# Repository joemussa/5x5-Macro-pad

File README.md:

# 5x5 Macro pad
 5x5 Macro Pad

1 Pi Pico
25 1N4148 SOD-323 (I'm an idiot and used 0805 footprint for the diodes but SOD-323 should fit this footprint)
25 Kailh MX Hotswap

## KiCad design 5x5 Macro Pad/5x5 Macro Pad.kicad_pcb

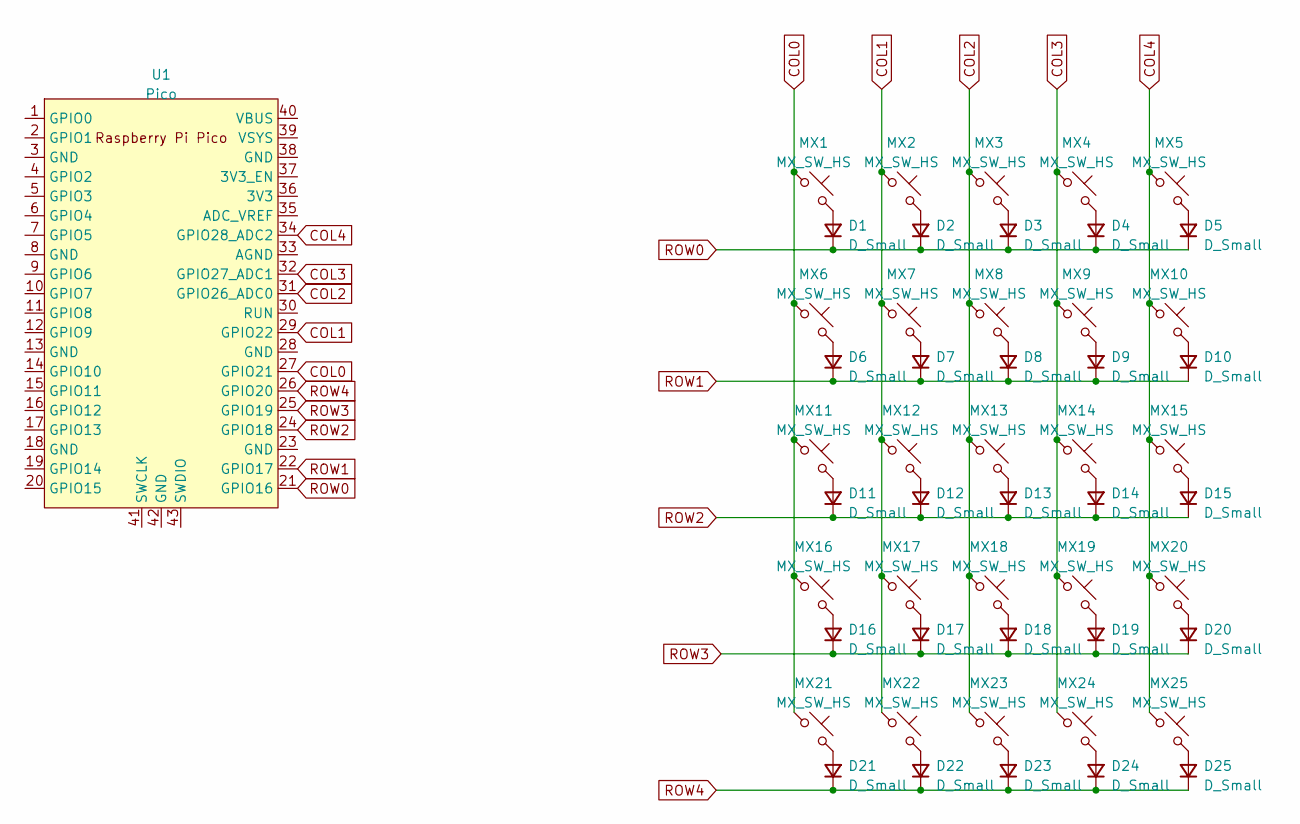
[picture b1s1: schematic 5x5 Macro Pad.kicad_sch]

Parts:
D1, D2, D3, D4, D5, D6, D7, D8, D9, D10, D11, D12, D13, D14, D15, D16, D17, D18, D19, D20, D21, D22, D23, D24, D25: D_Small; D_0805_2012Metric_Pad1.15x1.40mm_HandSolder
MX1, MX2, MX3, MX4, MX5, MX6, MX7, MX8, MX9, MX10, MX11, MX12, MX13, MX14, MX15, MX16, MX17, MX18, MX19, MX20, MX21, MX22, MX23, MX24, MX25: MX_SW_HS; SW_MX_HS_1u
U1: Pico; RPi_Pico_SMD_TH

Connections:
COL0: MX1.1, MX6.1, MX11.1, MX16.1, MX21.1, U1.27 (GPIO21)
COL1: MX2.1, MX7.1, MX12.1, MX17.1, MX22.1, U1.29 (GPIO22)
COL2: MX3.1, MX8.1, MX13.1, MX18.1, MX23.1, U1.31 (GPIO26_ADC0)
COL3: MX4.1, MX9.1, MX14.1, MX19.1, MX24.1, U1.32 (GPIO27_ADC1)
COL4: MX5.1, MX10.1, MX15.1, MX20.1, MX25.1, U1.34 (GPIO28_ADC2)
unnamed: D1.2 (A), MX1.2
unnamed: D2.2 (A), MX2.2
unnamed: D3.2 (A), MX3.2
unnamed: D4.2 (A), MX4.2
unnamed: D5.2 (A), MX5.2
unnamed: D6.2 (A), MX6.2
unnamed: D7.2 (A), MX7.2
unnamed: D8.2 (A), MX8.2
unnamed: D9.2 (A), MX9.2
unnamed: D10.2 (A), MX10.2
unnamed: D11.2 (A), MX11.2
unnamed: D12.2 (A), MX12.2
unnamed: D13.2 (A), MX13.2
unnamed: D14.2 (A), MX14.2
unnamed: D15.2 (A), MX15.2
unnamed: D16.2 (A), MX16.2
unnamed: D17.2 (A), MX17.2
unnamed: D18.2 (A), MX18.2
unnamed: D19.2 (A), MX19.2
unnamed: D20.2 (A), MX20.2
unnamed: D21.2 (A), MX21.2
unnamed: D22.2 (A), MX22.2
unnamed: D23.2 (A), MX23.2
unnamed: D24.2 (A), MX24.2
unnamed: D25.2 (A), MX25.2
ROW0: D1.1 (K), D2.1 (K), D3.1 (K), D4.1 (K), D5.1 (K), U1.21 (GPIO16)
ROW1: D6.1 (K), D7.1 (K), D8.1 (K), D9.1 (K), D10.1 (K), U1.22 (GPIO17)
ROW2: D11.1 (K), D12.1 (K), D13.1 (K), D14.1 (K), D15.1 (K), U1.24 (GPIO18)
ROW3: D16.1 (K), D17.1 (K), D18.1 (K), D19.1 (K), D20.1 (K), U1.25 (GPIO19)
ROW4: D21.1 (K), D22.1 (K), D23.1 (K), D24.1 (K), D25.1 (K), U1.26 (GPIO20)

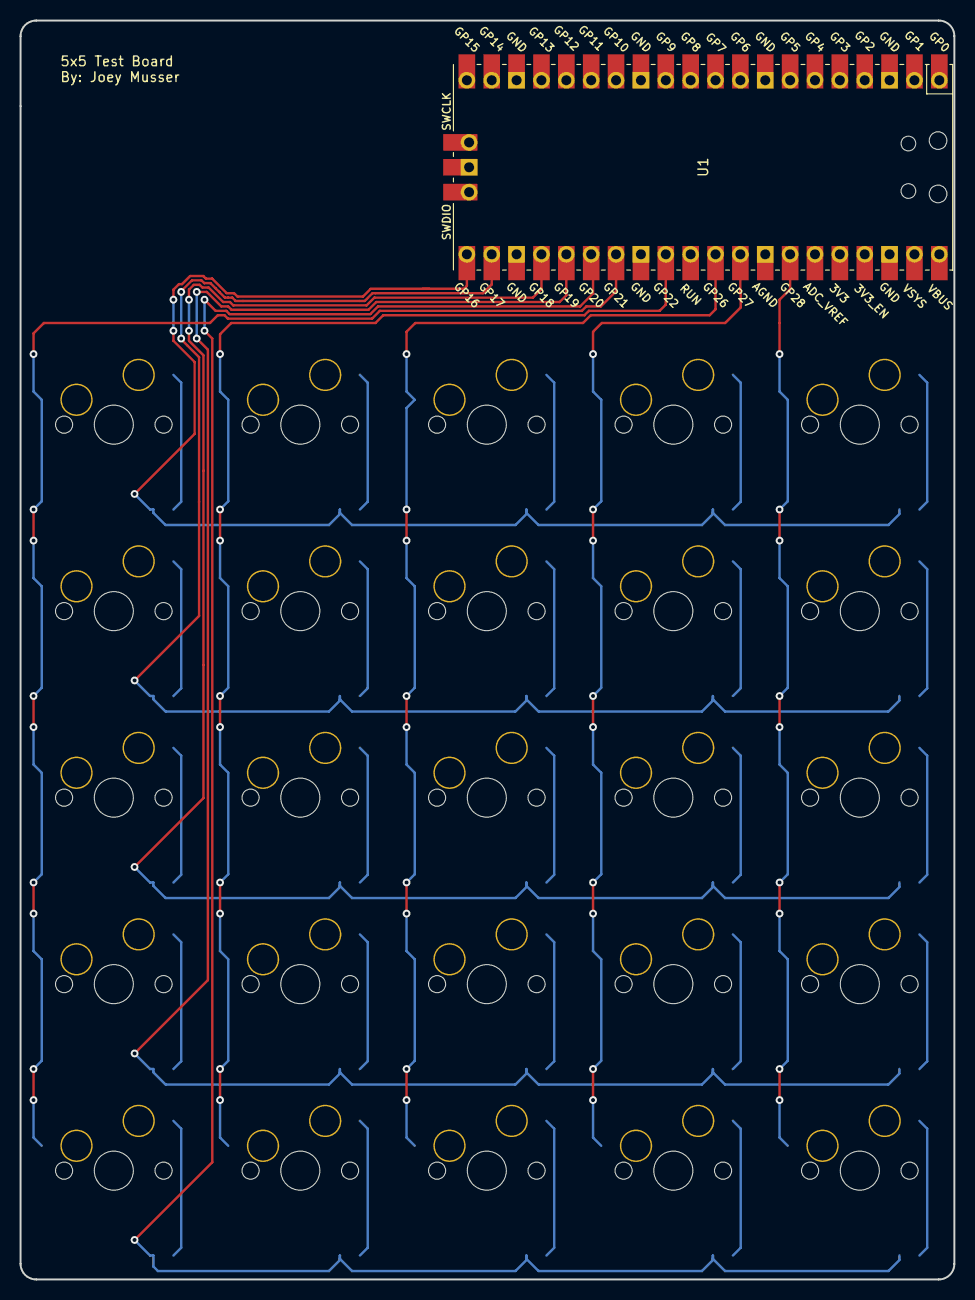
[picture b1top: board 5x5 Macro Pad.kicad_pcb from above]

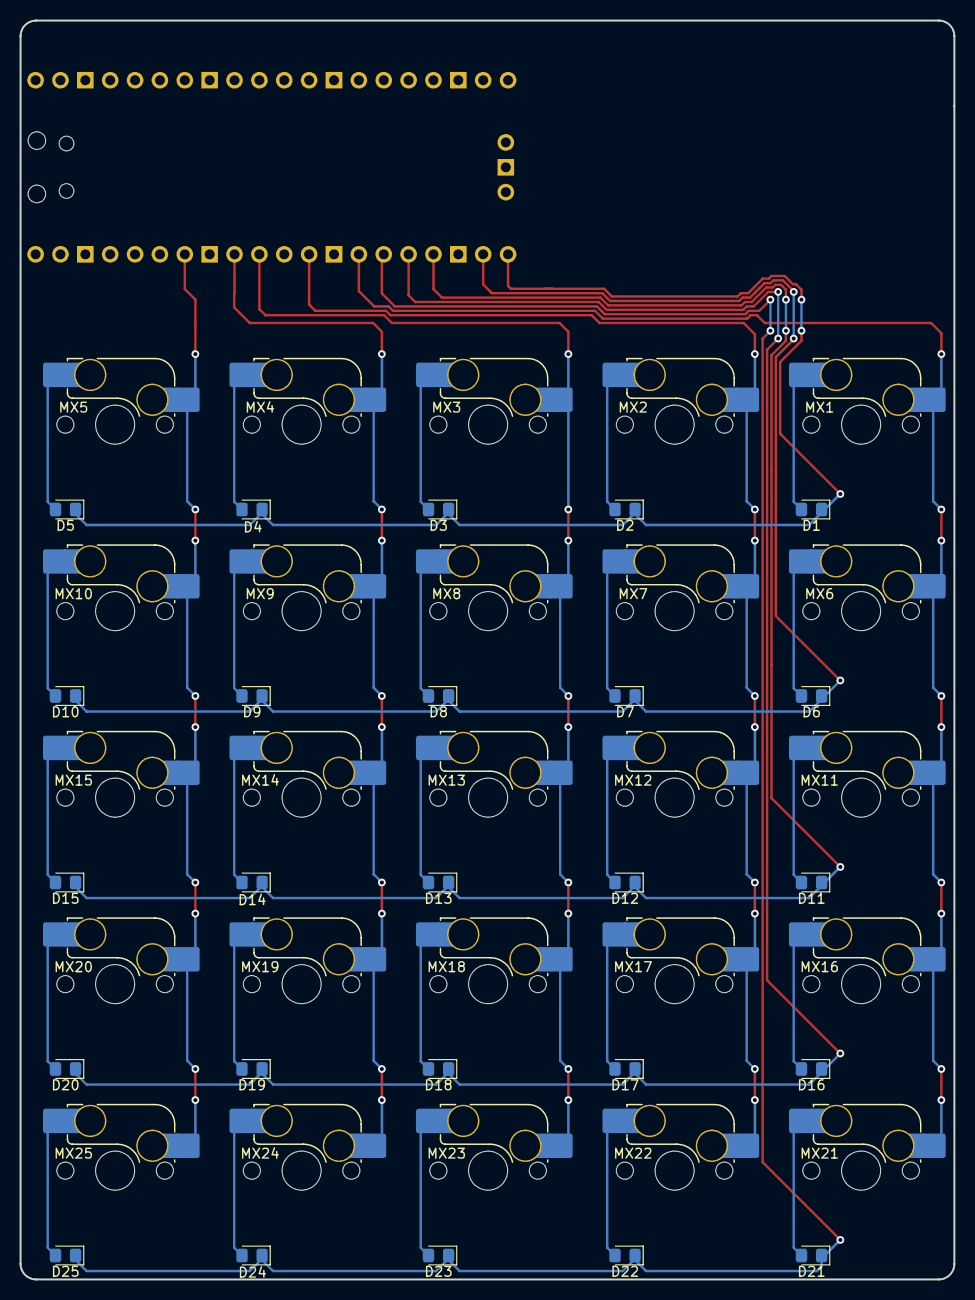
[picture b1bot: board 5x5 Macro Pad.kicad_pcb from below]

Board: 2 copper layers, 95.4 x 128.6 mm, 51 parts (50 on the bottom side), 35 nets.

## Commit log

2023-04-16 Project creation an init
2023-04-16 Finished
    Wired and gerbers generated.
